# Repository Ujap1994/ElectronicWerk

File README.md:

# ElectronicWerk

An open-source ECAD suite for beginners and advanced hobbyists. It covers
schematic, symbol, footprint and layout editing, a live 3D view, ERC/DRC,
manufacturing outputs, online part search, KiCad and Eagle exchange and a
full CLI.

> **Status:** early development. Version 0.15 opens ElectronicWerk to other
> tools: **Eagle import**, **KiCad export**, **external autorouters**
> (Specctra DSN/SES, Freerouting), **Gerber files as a reference drawing**
> and **DXF drawings** of the outline and mechanical layers. The GitHub
> integration stays switched off while its sign-in is reviewed: projects
> live on your computer.
> It builds on the assembly assistant, panels, statistics and documentation
> (0.14), scripts and AI agents (0.13), GitHub (0.12), the online part
> libraries (0.11), the 3D view (0.10), manufacturing outputs (0.9), the
> layout editor (0.8), the library editors (0.7), the schematic editor (0.6),
> the base library (0.5), the KiCad import (0.4), the fast 2D view (0.3) and
> projects (0.2).
> See the [roadmap](ROADMAP.md) for milestones and progress.

**[Documentation](https://ujap1994.github.io/ElectronicWerk/)** ·
**[Download](https://github.com/Ujap1994/ElectronicWerk/releases/latest)** ·
**[Changelog](CHANGELOG.md)** · **[Contributing](CONTRIBUTING.md)**

## Available now

- An Altium/KiCad-style **project** that holds schematics, PCB, libraries,
  rules and output jobs, with a new-project wizard and templates, a project
  tree, project properties and text variables
- **Never lose work:** unlimited undo/redo, an autosave journal of every
  change, crash recovery and atomic saves
- A fast **2D view** for schematic sheets and boards, drawn by the graphics
  card: smooth pan and zoom (60 fps on a board with 5,000 parts), layers with
  colours and opacity, view from the bottom, click/box/lasso selection and a
  property inspector
- A **schematic editor** in the same view: symbols from the project and base
  libraries, wires with automatic junctions, buses, net, global and
  hierarchical labels, power ports, hierarchical sheets, dragging with
  rubber-banding, copy and paste across sheets, find and replace, net
  highlighting, annotation and an editable inspector; new projects bring
  starter symbols and a guide for a first schematic
- **Library editors** for symbols (pins, units, De Morgan bodies, a pin table
  with bulk edits and pasted pin lists), footprints (all pad kinds and
  shapes, pad arrays, silkscreen, fabrication and courtyard layers, 3D model
  alignment) and components (symbol, footprint, manufacturer, part number,
  suppliers), with **IPC-7351 footprint wizards** (chip, SOIC/QFP, QFN, BGA,
  headers) and KLC-like **library checks**
- A **net navigator**: Ctrl/⌘ + double-click on a net lists every place of it
  on every sheet and jumps there
- A **layout editor**: footprints, **interactive routing** that walks around
  copper of other nets with the clearances of the rules, vias and layer
  changes, dragging tracks, copper **zones** with thermal reliefs, priorities
  and island removal, keep-out areas, board outlines (drawn or **imported
  from DXF**), board presets and a stack-up editor, turning, flipping,
  aligning and an editable inspector
- **Advanced layout:** **push-and-shove** routing and dragging that keeps
  45° bends; **blind, buried and microvias**; **controlled impedance** with
  an impedance calculator (a beginner mode picks the interface, an advanced
  mode sets every value); **differential pairs** routed together;
  **length matching** with exact meanders; **teardrops**; **stitching vias**
  and via fences; **channels** that copy the layout of a repeated sheet;
  **assembly variants** for the outputs
- **Parts from datasheets:** open a part's PDF datasheet and get its symbol,
  an IPC-7351 footprint, a 3D STEP model and the component — pins, packages
  and dimensions are read from the datasheet and shown beside it for
  checking; a part already in a library is named instead; your own AI agent
  can help through MCP (no API key in the app)
- **Enclosure check:** place the STEP files of the enclosure, lid, panels
  and screws around the board in 3D (or make a box that fits) and find
  collisions, too small clearances, mounting holes without bosses and
  connectors without an opening while you lay out; take the board outline
  and height areas from the enclosure; export the whole assembly as STEP
- A **part catalog**: complete parts (symbol, footprint and 3D model) sorted
  into categories — passive parts, semiconductors, ICs by function and
  microcontrollers by vendor, connectors, … — with a choice of the common
  packages for basic parts (0402 … 1206, pin headers, JST, …); place a part
  on the schematic with its package in two clicks
- **Everyday tools:** a **selection filter**, **select similar** and
  editing many objects at once, a **net inspector** (class, length, vias,
  open connections of every net), **net colours** on sheets and boards,
  **groups**, your own **keyboard shortcuts**, **calculators** (voltage
  divider, regulator resistors, E series, track and via current after
  IPC-2152, fusing current) and **logos, pictures and QR codes** on
  silkscreen, copper or mask
- **Layout construction:** **dimensions** and leaders on the board, a
  **fabrication drawing** for the board maker (outline, drill table,
  stack-up and notes), **rooms** that hold the parts of a circuit block and
  scope design rules, a **creepage check** that follows the surface around
  slots and holes, **padstacks** per layer, **via filling** after IPC-4761
  with a via-in-pad check, and **design blocks** that carry a circuit with
  its routed layout into other projects
- **Systems of several boards:** a shield on a carrier, a main board with a
  front panel, boards of other projects or reference designs from KiCad and
  Eagle, joined by mating connectors or **cables**; a **connection check
  across the boards** finds swapped and different signals, supplies on
  signal pins and open pins, and renames a signal on every board at once;
  the boards are stacked on their connectors in 3D and checked for
  collisions; a system bill of materials, connection report, wiring lists,
  **harness drawings** and one STEP file
- **Design rules** with net classes, name patterns, board minimums and
  **custom rules** in a small query language (`A.netclass == 'HV' &&
B.netclass != 'HV'`)
- A **design rules check** that runs online while you edit (about 20 ms on a
  500-part board): clearances, shorts, unrouted connections, widths, vias,
  annular rings, holes, board edge, keep-outs, courtyards, silkscreen and
  parity with the schematic, with markers on the board and accepted findings
- **Schematic ↔ board:** update the board from the schematic (new parts,
  footprint and value changes, nets, renamed nets), back annotation of
  designators, values and footprints, and **cross-probing** between sheets
  and board
- An **electrical rules check** with KiCad's configurable pin type matrix,
  unconnected pins, conflicting drivers, missing power and more, a results
  panel that zooms to each problem, and the same results as KiCad on
  imported projects
- **Manufacturing outputs** in **output jobs** (like Altium's OutJobs): one
  click writes **Gerber X2** with net, pad and component attributes and a job
  file, **Excellon** drill files (plated, non-plated, blind and buried, slots),
  a drill map, a configurable **bill of materials** (CSV, XLSX, HTML),
  **pick-and-place** files, **IPC-D-356** and **IPC-2581** netlists, **PDF and
  SVG prints** of schematics, board layers and **assembly drawings**, and a
  ZIP package; **presets** for JLCPCB, PCBWay, AISLER, Eurocircuits and OSH
  Park; the Gerber output is verified pixel by pixel against KiCad 10
- **Panels** made by the output job: copies of the board in rows and
  columns, separated by mouse bites or V-score, with rails, fiducials and
  tooling holes, and a live preview; Gerber, drill and pick-and-place files
  are written for the panel
- **Project documentation:** one self-contained HTML file with the sheets,
  board views, assembly drawings, stack-up, bill of materials, holes and
  **design statistics** (also in the project details and on the CLI)
- An **assembly assistant** for soldering by hand: the parts in groups of
  equal parts, the next ones highlighted on the board, a checklist that is
  saved at once, a workbench mode with large text and its own window for a
  second monitor
- A built-in **Gerber viewer** for Gerber X2/RS-274X and Excellon files from
  any tool
- A **live 3D view** of the board — laminate, copper with its surface finish,
  solder mask, silkscreen and the parts' 3D models — that follows every edit
  at once, in a tab or **in its own window** for a second monitor, with
  camera presets, sections, measuring, screenshots and a selection shared
  with the layout editor; models come from the project, a KiCad installation
  or the base library
- **3D exports:** **STEP** assemblies for mechanical CAD (the board as an exact
  solid with true cylinders for holes, the parts' original STEP models),
  **GLB** and **VRML**, from the 3D view, output jobs or the CLI; part
  placement verified against KiCad 10, the STEP file read back with
  OpenCASCADE in every CI run
- **Exports:** KiCad and CSV netlists, a bill of materials, SVG and a PDF of
  all sheets
- **KiCad import:** KiCad 6 to 10 projects with schematics, hierarchy,
  symbols, board, footprints, zones, rules and project libraries become an
  ElectronicWerk project in one step, with a detailed import report; KiCad
  libraries can be added to a project at any time
- **Eagle import:** Eagle 6 to 9 schematics, boards and libraries (XML)
  become native projects with an import report; nets are kept exactly,
  mirrored parts land on the bottom, `.lbr` libraries go through the
  duplicate check
- **KiCad export:** every project as a KiCad project (KiCad 8 format, opened
  by KiCad 8 to 10) with all sheets, the board, the project libraries and
  the design rules; checked by a round trip and by KiCad itself
- **External autorouters:** the board as a Specctra DSN file for
  Freerouting and others, the routed session (SES) back as one undo step
- **Gerber files as a reference drawing** on user layers, and **DXF
  drawings** of the outline and mechanical layers for mechanical CAD
- **Netlists** from KiCad (`.net`, XML) and CSV: compare them with a board by
  connectivity and apply them
- A **base library** with the KiCad symbols, footprints and 3D models (about
  45,000 entries): full-text search in milliseconds, filters, 2D and 3D
  previews, adding parts to a project; downloaded on demand or built from a
  local KiCad installation
- **Online part libraries:** parts downloaded from **SnapEDA** and **Ultra
  Librarian** (in an isolated provider window or any browser) are imported
  with symbol, footprint and 3D model, and checked against the base library
- **GitHub and source control** (switched off in this version, see
  [GitHub](https://ujap1994.github.io/ElectronicWerk/guide/github)) without
  installing git: projects on GitHub, commit, push, pull, branches, history
  and "Open from GitHub"; sign-in through a GitHub App that may only use the
  repositories you choose, with 8-hour tokens kept in the system keychain, or
  a fine-grained token. Pulls never merge inside a file, so a design is never
  half merged
- **Duplicate detection** independent of the source: exact duplicates are
  merged, near duplicates (pads within 0.05 mm, same mesh in other colours, …)
  are reviewed side by side, with a reproducible report
- An open, **git-friendly file format**: readable JSON, one object per line,
  with schema versions and migrations
- A **CLI** (`ewerk`) for everything: create projects, place parts and
  connect pins by name (`R1.2`, `U1.VCC`), update, place and route boards, run
  the ERC and DRC with exit codes for CI, generate outputs, import KiCad
  projects and libraries, export 3D models and manage the base library;
  scripts in JSON Lines, a JSON-RPC 2.0 session and an **MCP server** so AI
  agents (Claude, Cursor, VS Code, …) can design boards
- A German and English UI, light and dark appearance, a command palette and
  an update notice
- Builds for Windows, macOS and Linux

## Planned highlights

- **Layout construction and routing:** dimensions and a fabrication drawing,
  design blocks, rooms, a creepage check, padstacks, fan-out, bus routing,
  arc tracks and a built-in autorouter
- **Exchange:** ODB++, Gerber back to a board, comparing two versions
- Hardening for version 1.0 on real designs: performance, stability,
  a walkthrough of every workflow and acceptance on real boards

## License

The application code is licensed under the [MIT License](LICENSE). Library
data derived from third-party libraries keeps its original license (for
example, the KiCad libraries are CC-BY-SA 4.0 with a design exception).

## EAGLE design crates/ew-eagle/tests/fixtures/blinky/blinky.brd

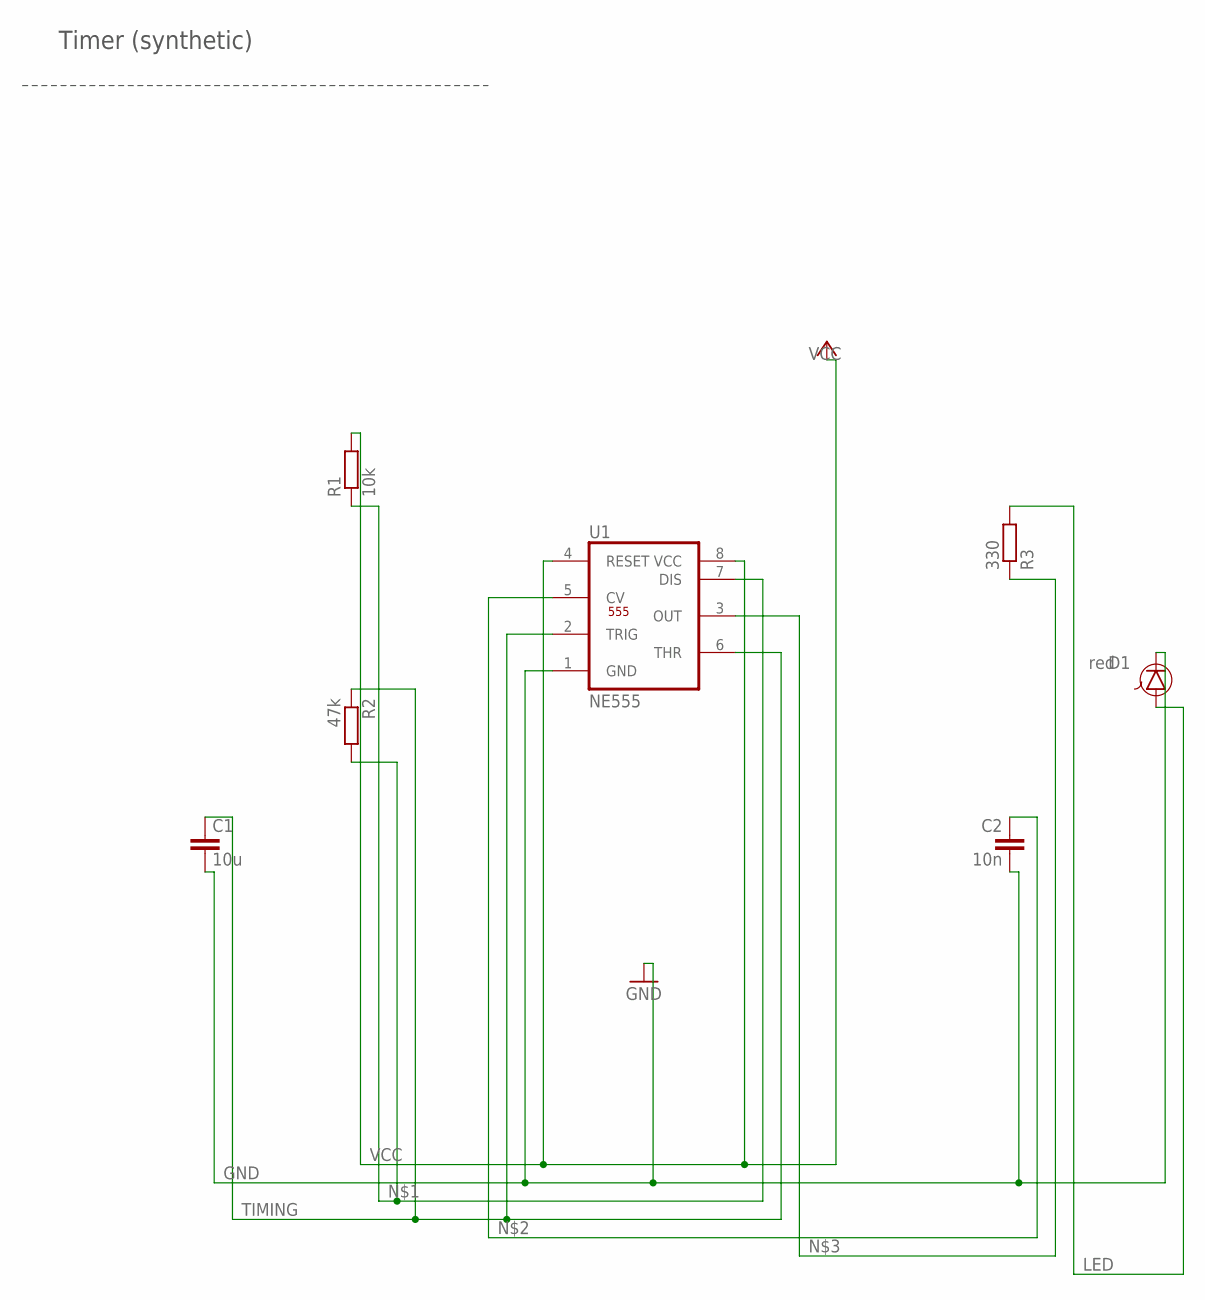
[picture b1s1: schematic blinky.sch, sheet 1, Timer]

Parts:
C1: 10u; C0603
C2: 10n; C0603
D1: red; LED3MM
R1: 10k; R0805
R2: 47k; R0805
R3: 330; R0805
U1: NE555; SO08; MPN NE555DR

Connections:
GND: C1.2, C2.2, D1.C, U1.1 (GND); also elsewhere on the board
LED: D1.A, R3.2
unnamed: R1.1, R2.2, U1.7 (DIS)
unnamed: C2.1, U1.5 (CV)
unnamed: R3.1, U1.3 (OUT)
TIMING: C1.1, R2.1, U1.2 (TRIG), U1.6 (THR)
VCC: R1.2, U1.4 (RESET), U1.8 (VCC); also elsewhere on the board

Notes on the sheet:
Timer (synthetic)

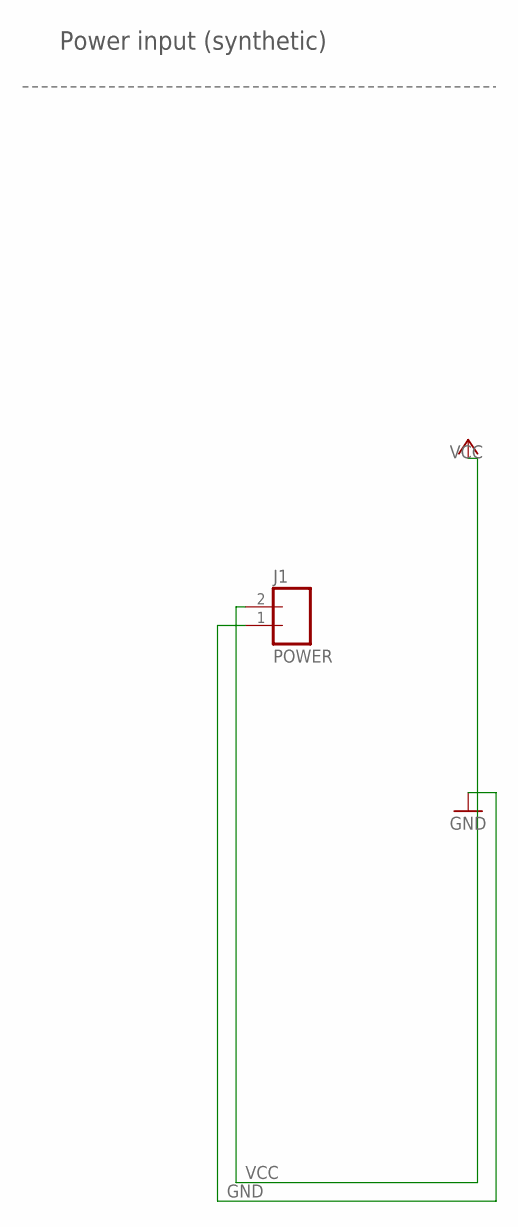
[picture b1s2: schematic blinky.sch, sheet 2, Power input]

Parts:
J1: POWER; HDR2

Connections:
GND: J1.1; also elsewhere on the board
VCC: J1.2; also elsewhere on the board

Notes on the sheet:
Power input (synthetic)

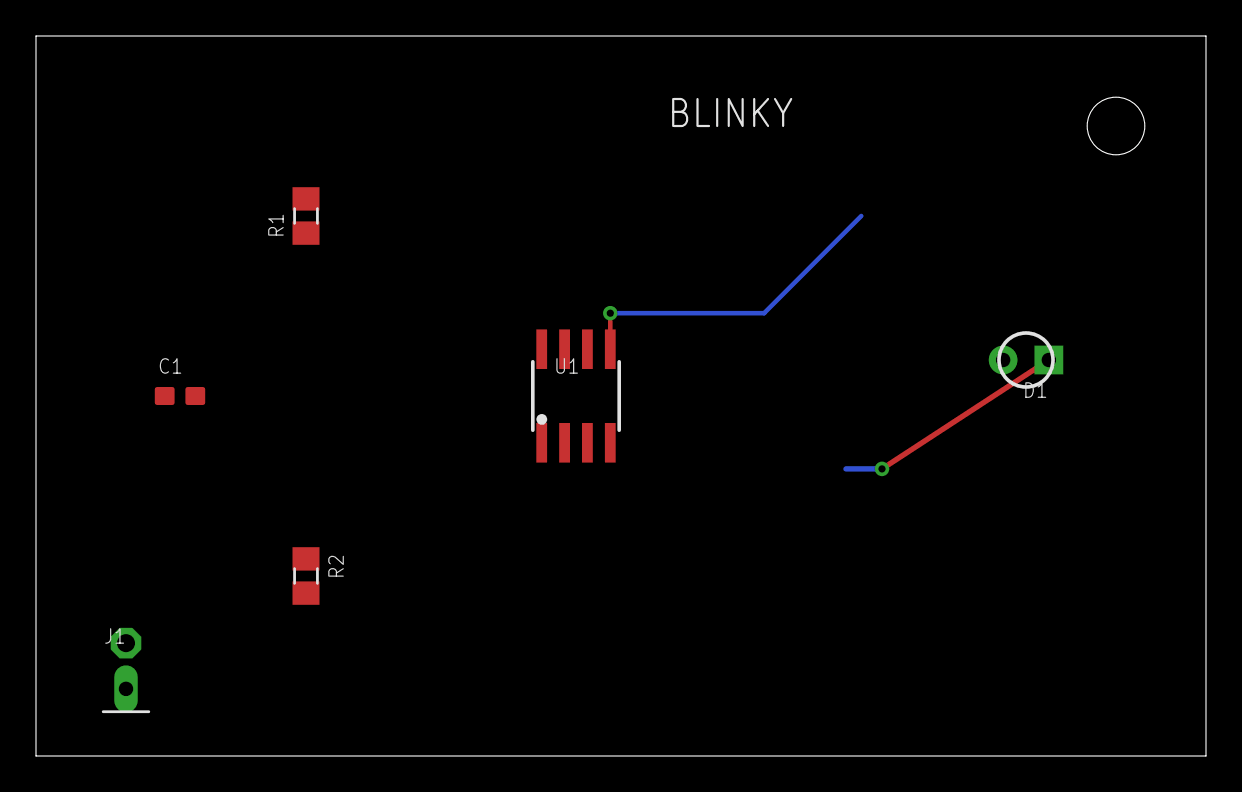
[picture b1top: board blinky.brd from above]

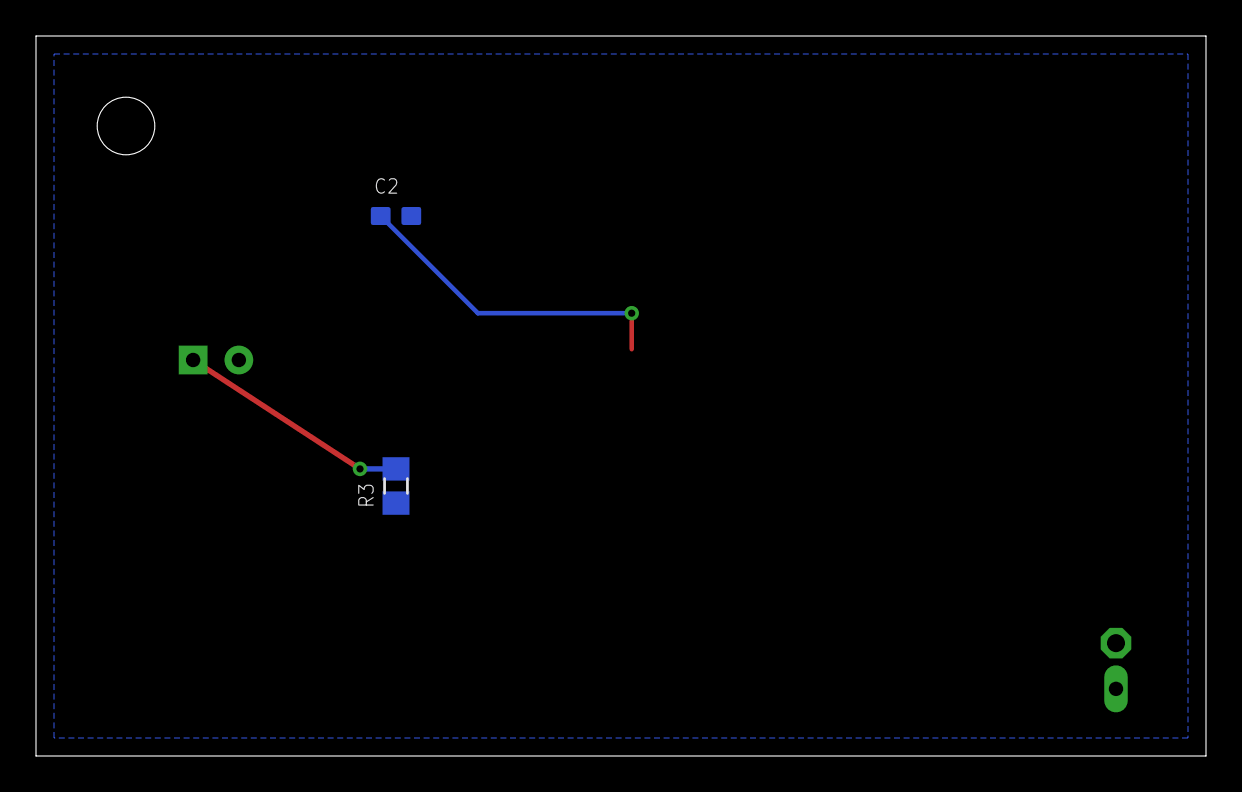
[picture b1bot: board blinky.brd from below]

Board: 2 copper layers, 65.0 x 40.0 mm, 8 parts (2 on the bottom side), 7 nets.
